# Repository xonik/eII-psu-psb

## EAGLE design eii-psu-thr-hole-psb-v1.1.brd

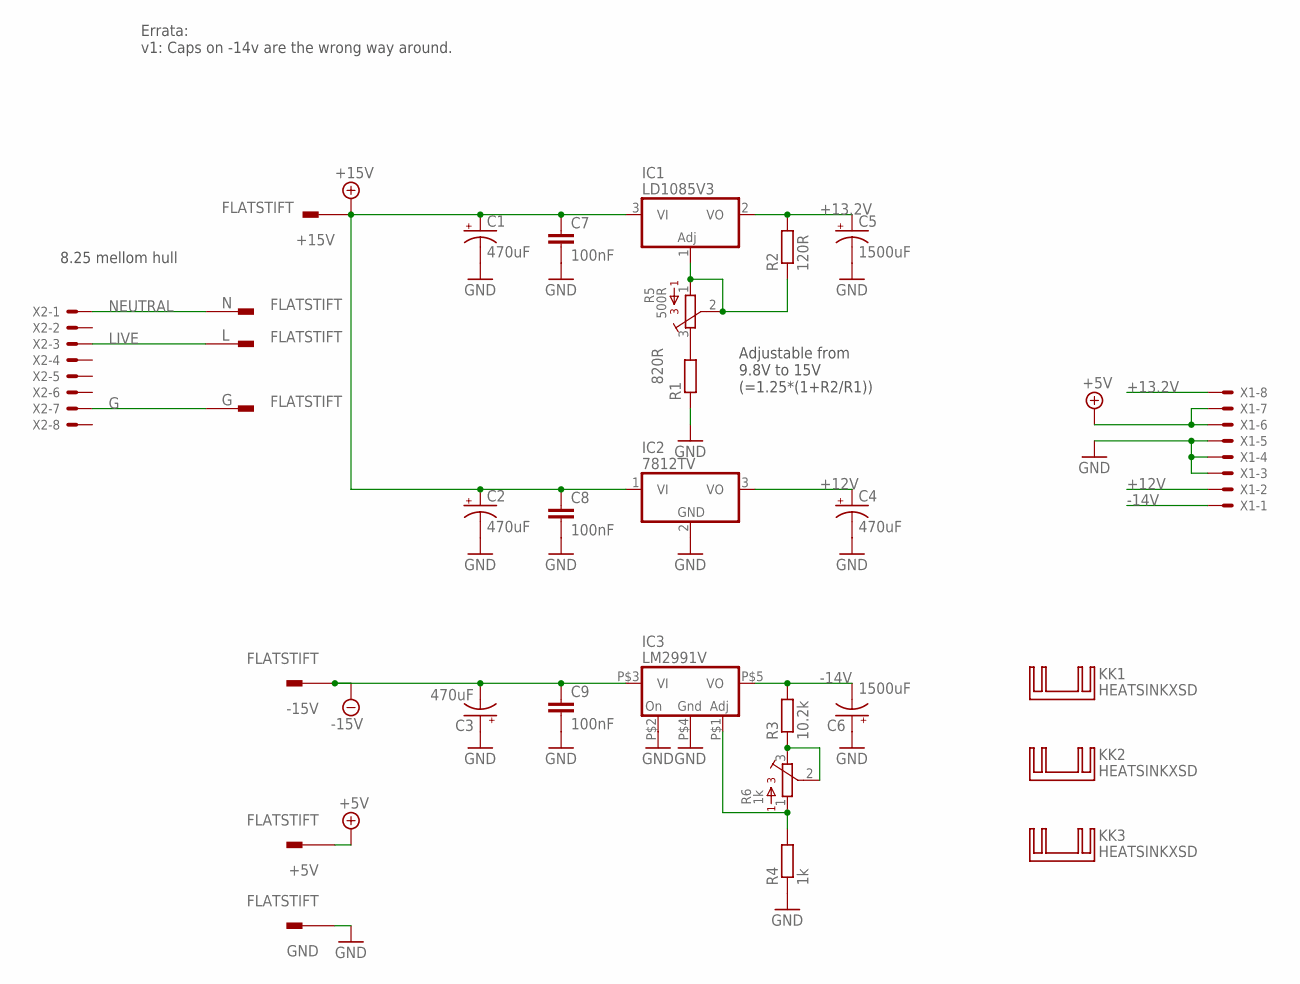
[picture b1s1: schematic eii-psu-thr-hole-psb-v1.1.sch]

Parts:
+5V, +15V: FLATSTIFT
-15V: FLATSTIFT
C1, C2, C3, C4: 470uF; E5-10,5
C5, C6: 1500uF; E5-13
C7, C8, C9: 100nF; C050-030X075
G: FLATSTIFT
GND: FLATSTIFT
IC1: LD1085V3; TO220V-J
IC2: 7812TV; TO220V
IC3: LM2991V; TO220-5V-J
KK1, KK2, KK3: HEATSINKXSD; XSD1226-005
L: FLATSTIFT
N: FLATSTIFT
R1: 820R; 0207/7
R2: 120R; 0207/7
R3: 10.2k; 0207/7
R4: 1k; 0207/7
R5: 500R; 3362P
R6: 1k; 3362P
X1, X2: KK-156-8

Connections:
+5V: +5V.F, +5V.F2, X1.6, X1.7
+12V: C4.+, IC2.3 (VO), X1.2
+13.2V: C5.+, IC1.2 (VO), R2.2, X1.8
+15V: +15V.F, +15V.F2, C1.+, C2.+, C7.1, C8.1, IC1.3 (VI), IC2.1 (VI)
-14V: C6.-, IC3.P$5 (VO), R3.2, X1.1
-15V: -15V.F, -15V.F2, C3.-, C9.1, IC3.P$3 (VI)
G: G.F, G.F2, X2.7
GND: C1.-, C2.-, C3.+, C4.-, C5.-, C6.+, C7.2, C8.2, C9.2, GND.F, GND.F2, IC2.2 (GND), IC3.P$2 (ON), IC3.P$4 (GND), R1.1, R4.1, X1.3, X1.4, X1.5
LIVE: L.F, L.F2, X2.3
unnamed: R1.2, R5.3
unnamed: IC1.1 (ADJ), R2.1, R5.1, R5.2
unnamed: R3.1, R6.2, R6.3
unnamed: IC3.P$1 (ADJ), R4.2, R6.1
NEUTRAL: N.F, N.F2, X2.1

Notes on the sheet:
Adjustable from 9.8V to 15V (=1.25*(1+R2/R1))
8.25 mellom hull
Errata: v1: Caps on -14v are the wrong way around.

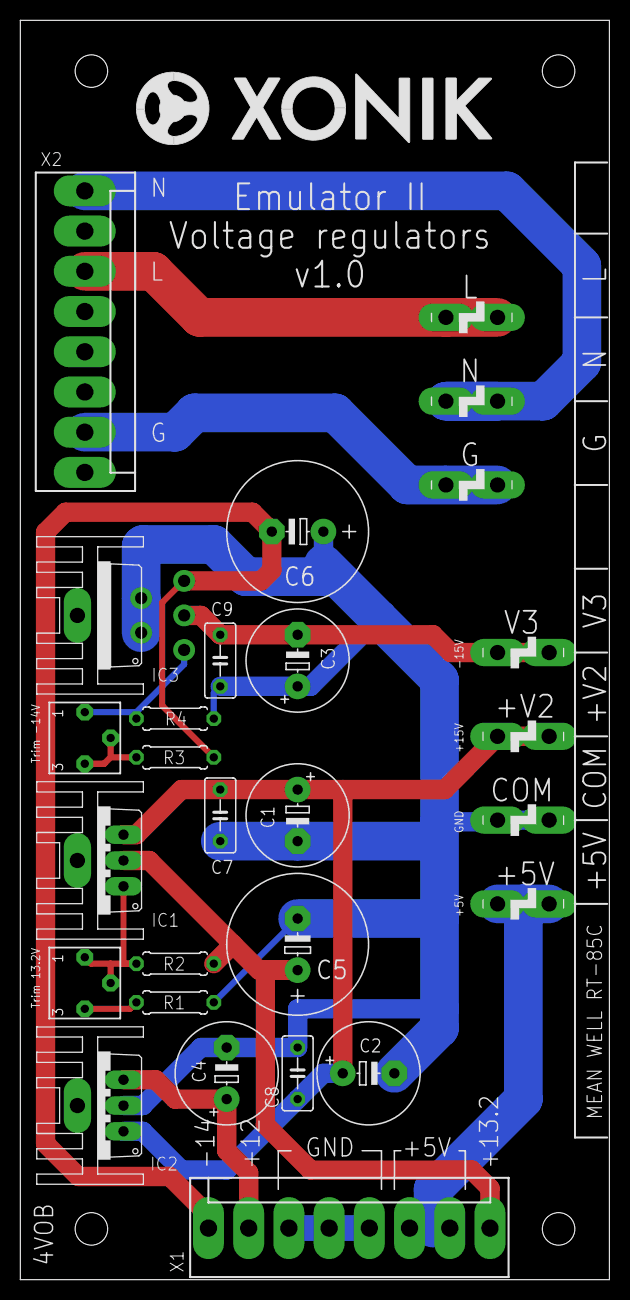
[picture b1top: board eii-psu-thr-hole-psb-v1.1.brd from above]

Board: 2 copper layers, 58.0 x 124.0 mm, 31 parts (0 on the bottom side), 14 nets.

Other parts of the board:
U$3: XONIK_LOGO_35

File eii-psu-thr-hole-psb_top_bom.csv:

Comment,Designator,Footprint,LCSC Part #
1k,R4,0207/7,C433532
1k,R6,3362P,C118947
10k,R3,0207/7,C410695
100nF,C7 C8 C9,C050-030X075,C333838
120R,R2,0207/7,C433527
470uF,C1 C2 C3 C4,E5-10.5,C338188
500R,R5,3362P,C118916
820R,R1,0207/7,C410580
1500uF,C5 C6,E5-13,C107417
HEATSINKXSD,KK1 KK2 KK3,XSD1226-005,C116600
LD1085V3,IC1,TO220V-J,
LM2991V,IC3,TO220-5V-J,
KK-156-8,X1 X2,KK-156-8,C138436
F061,+5V +15V -15V GND G L N,FLATSTIFT,C86469

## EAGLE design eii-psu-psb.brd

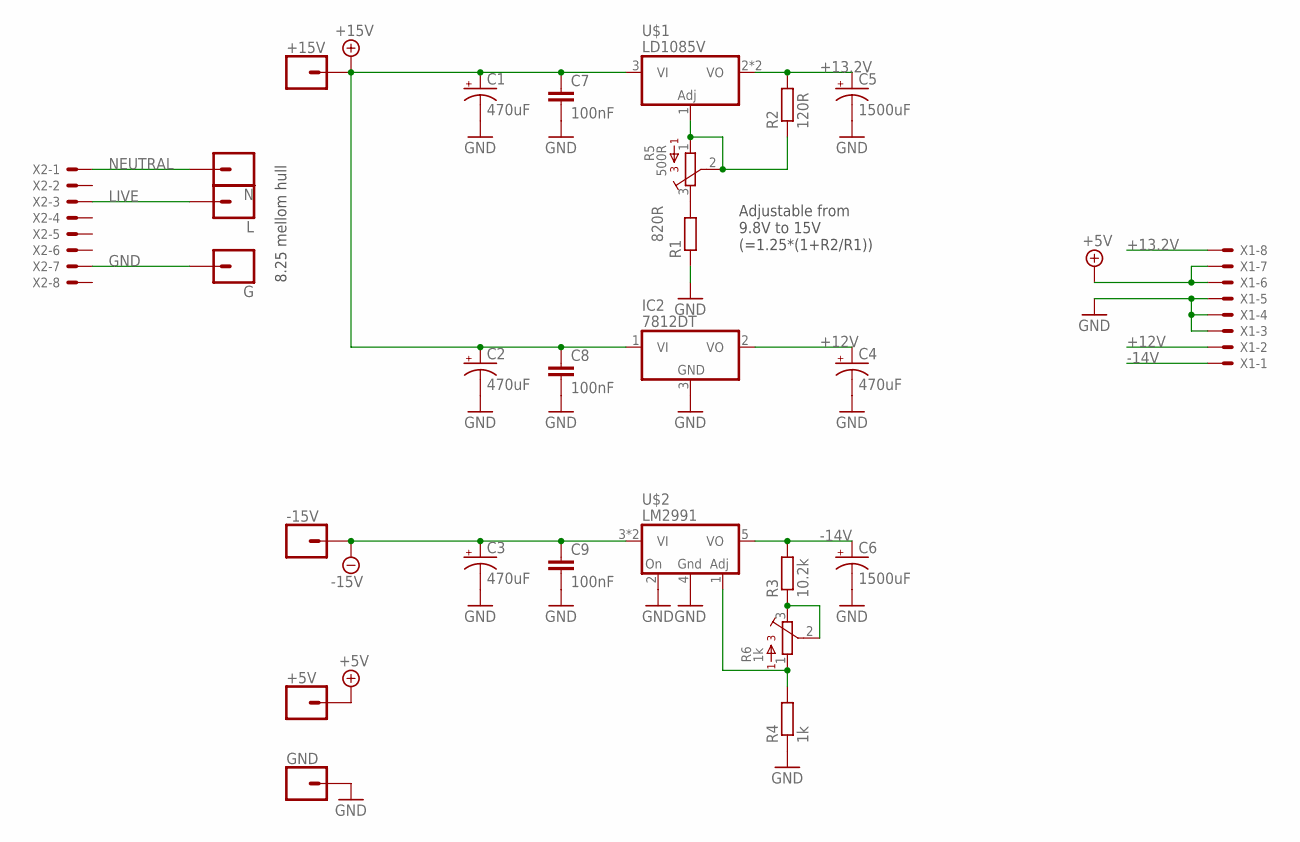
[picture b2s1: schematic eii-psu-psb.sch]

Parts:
+5V, +15V: CONN_01PTH_2MM; 1X01_2MM
-15V: CONN_01PTH_2MM; 1X01_2MM
C1, C2, C3, C4: 470uF; E5-10,5
C5, C6: 1500uF; E5-13
C7, C8, C9: 100nF; C050-030X075
G: CONN_01PTH_2MM; 1X01_2MM
GND: CONN_01PTH_2MM; 1X01_2MM
IC2: 7812DT; TO252
L: CONN_01PTH_2MM; 1X01_2MM
N: CONN_01PTH_2MM; 1X01_2MM
R1: 820R; R1206
R2: 120R; R1206
R3: 10.2k; R1206
R4: 1k; R1206
R5: 500R; 3362P
R6: 1k; 3362P
U$1: LD1085V; TO263-3J
U$2: LM2991; TO263-5J
X1, X2: KK-156-8

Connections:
+5V: +5V.1, X1.6, X1.7
+12V: C4.+, IC2.2 (VO), X1.2
+13.2V: C5.+, R2.2, U$1.2 (VO), U$1.TAB (VO), X1.8
+15V: +15V.1, C1.+, C2.+, C7.1, C8.1, IC2.1 (VI), U$1.3 (VI)
-14V: C6.+, R3.2, U$2.5 (VO), X1.1
-15V: -15V.1, C3.+, C9.1, U$2.3 (VI), U$2.6 (VI)
GND: C1.-, C2.-, C3.-, C4.-, C5.-, C6.-, C7.2, C8.2, C9.2, G.1, GND.1, IC2.3 (GND), R1.1, R4.1, U$2.2 (ON), U$2.4 (GND), X1.3, X1.4, X1.5, X2.7
LIVE: L.1, X2.3
unnamed: R1.2, R5.3
unnamed: R2.1, R5.1, R5.2, U$1.1 (ADJ)
unnamed: R3.1, R6.2, R6.3
unnamed: R4.2, R6.1, U$2.1 (ADJ)
NEUTRAL: N.1, X2.1

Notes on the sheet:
Adjustable from 9.8V to 15V (=1.25*(1+R2/R1))
8.25 mellom hull

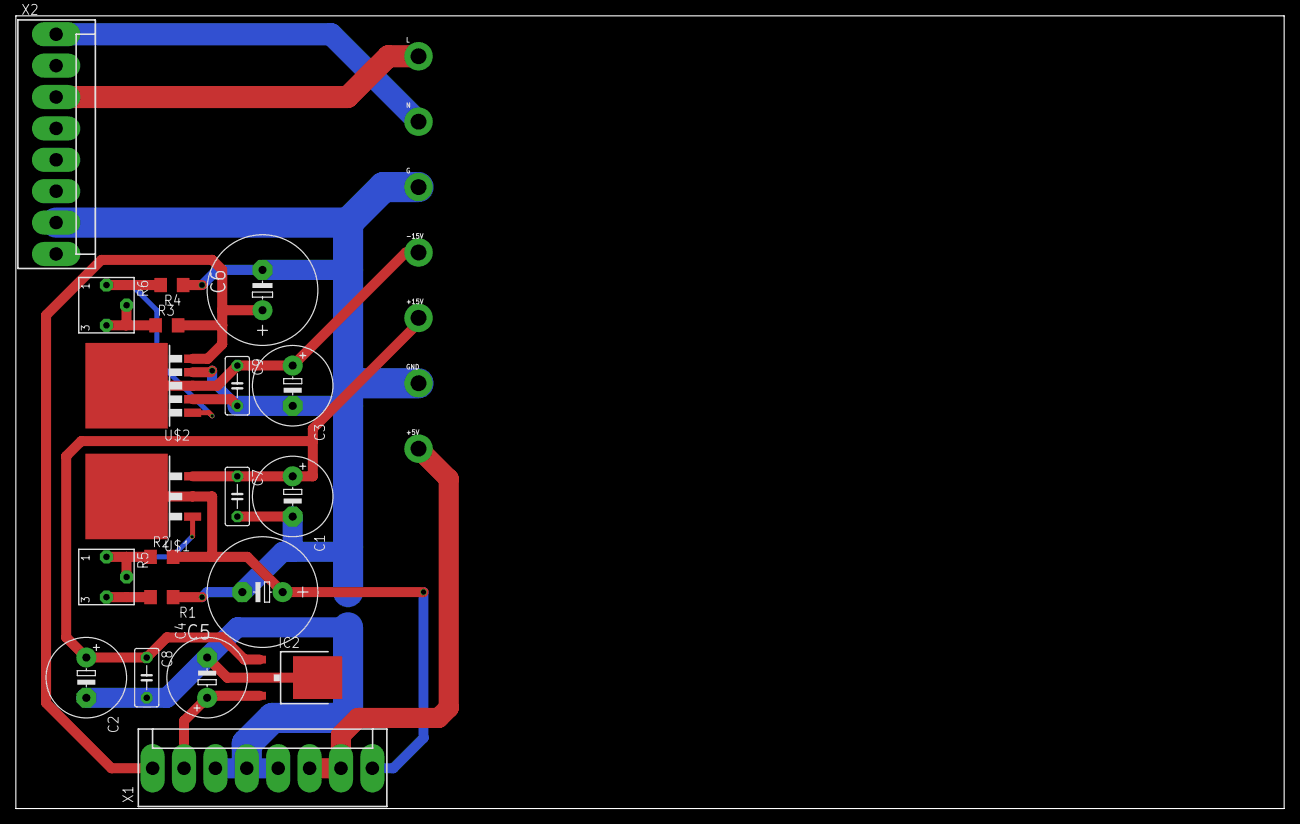
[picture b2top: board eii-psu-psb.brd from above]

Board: 2 copper layers, 160.0 x 100.0 mm, 27 parts (0 on the bottom side), 13 nets.

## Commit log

2021-08-31 First version, need to place things properly
2021-12-21 Through hole version
2021-12-22 Switched to through-hole resistors too
2021-12-22 Removed crossing neutral/live
2021-12-25 New heat sinks, better silk screen
2021-12-25 Tweaks after uploading to JLCPCB
2021-12-28 Added all parts except regulators
2022-01-07 Added tray to be laser cut
2022-04-08 moving to new pc

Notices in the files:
parts and their libraries:
SparkFun-Connectors: Licensing: Creative Commons ShareAlike 4.0 International - https://creativecommons.org/licenses/by-sa/4.0
